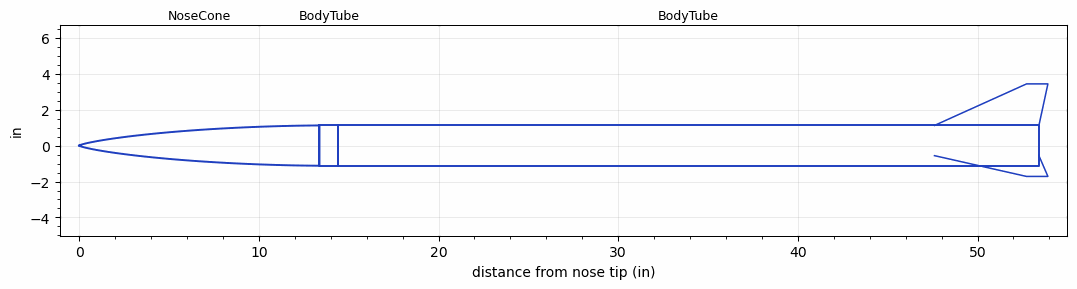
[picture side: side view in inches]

<RASAeroDocument>
 <FileVersion>2</FileVersion>
 <RocketDesign>
  <NoseCone>
   <Length>13.375</Length>
   <Diameter>2.241</Diameter>
   <Shape>LV-Haack</Shape>
   <Location>0</Location>
  </NoseCone>
  <BodyTube>
   <Length>1.0415</Length>
   <Diameter>2.241</Diameter>
   <Location>13.375</Location>
  </BodyTube>
  <BodyTube>
   <Length>39</Length>
   <Diameter>2.241</Diameter>
   <Location>14.4165</Location>
   <Fin>
    <Count>3</Count>
    <Chord>5.813</Chord>
    <Span>2.313</Span>
    <SweepDistance>5.125</SweepDistance>
    <TipChord>1.188</TipChord>
    <Thickness>0.124</Thickness>
    <Location>5.813</Location>
    <AirfoilSection>Hexagonal Blunt Base</AirfoilSection>
    <FX1>0.5</FX1>
   </Fin>
  </BodyTube>
  <Surface>Smooth Paint</Surface>
  <ModifiedBarrowman>True</ModifiedBarrowman>
  <Turbulence>False</Turbulence>
  <UseBooster1>False</UseBooster1>
  <UseBooster2>False</UseBooster2>
 </RocketDesign>
 <LaunchSite>
  <Altitude>1250</Altitude>
  <Pressure>0</Pressure>
  <RodAngle>0</RodAngle>
  <RodLength>6</RodLength>
  <Temperature>90</Temperature>
  <WindSpeed>10</WindSpeed>
 </LaunchSite>
 <Recovery>
  <Altitude1>1000</Altitude1>
  <Altitude2>500</Altitude2>
  <DeviceType1>Parachute</DeviceType1>
  <DeviceType2>Parachute</DeviceType2>
  <Event1>True</Event1>
  <Event2>True</Event2>
  <Size1>6</Size1>
  <Size2>36</Size2>
  <EventType1>Apogee</EventType1>
  <EventType2>Altitude</EventType2>
  <CD1>0.5</CD1>
  <CD2>0.98</CD2>
 </Recovery>
 <SimulationList>
  <Simulation>
   <SustainerEngine>K590  (CTI)</SustainerEngine>
   <SustainerLaunchWt>6.63</SustainerLaunchWt>
   <SustainerCG>32.84</SustainerCG>
   <SustainerIgnitionDelay>0</SustainerIgnitionDelay>
   <Booster1SeparationDelay>0</Booster1SeparationDelay>
   <Booster1IgnitionDelay>0</Booster1IgnitionDelay>
   <IncludeBooster1>False</IncludeBooster1>
   <Booster2Delay>0</Booster2Delay>
   <IncludeBooster2>False</IncludeBooster2>
   <TimetoApogee>32.44056</TimetoApogee>
   <MaxAltitude>24973.27</MaxAltitude>
   <MaxVelocity>2311.566</MaxVelocity>
  </Simulation>
  <Simulation>
   <SustainerEngine>K660  (CTI)</SustainerEngine>
   <SustainerLaunchWt>6.69</SustainerLaunchWt>
   <SustainerCG>31.59</SustainerCG>
   <SustainerIgnitionDelay>0</SustainerIgnitionDelay>
   <Booster1SeparationDelay>0</Booster1SeparationDelay>
   <Booster1IgnitionDelay>0</Booster1IgnitionDelay>
   <IncludeBooster1>False</IncludeBooster1>
   <Booster2Delay>0</Booster2Delay>
   <IncludeBooster2>False</IncludeBooster2>
   <TimetoApogee>32.29059</TimetoApogee>
   <MaxAltitude>24734.03</MaxAltitude>
   <MaxVelocity>2468.057</MaxVelocity>
  </Simulation>
  <Simulation>
   <SustainerEngine>J380SS  (CTI)</SustainerEngine>
   <SustainerLaunchWt>5.23</SustainerLaunchWt>
   <SustainerCG>33.03</SustainerCG>
   <SustainerIgnitionDelay>0</SustainerIgnitionDelay>
   <Booster1SeparationDelay>0</Booster1SeparationDelay>
   <Booster1IgnitionDelay>0</Booster1IgnitionDelay>
   <IncludeBooster1>False</IncludeBooster1>
   <Booster2Delay>0</Booster2Delay>
   <IncludeBooster2>False</IncludeBooster2>
   <TimetoApogee>24.22046</TimetoApogee>
   <MaxAltitude>11923.27</MaxAltitude>
   <MaxVelocity>1436.021</MaxVelocity>
  </Simulation>
  <Simulation>
   <SustainerEngine>K260-CL  (CTI)</SustainerEngine>
   <SustainerLaunchWt>6.88</SustainerLaunchWt>
   <SustainerCG>31.73</SustainerCG>
   <SustainerIgnitionDelay>0</SustainerIgnitionDelay>
   <Booster1SeparationDelay>0</Booster1SeparationDelay>
   <Booster1IgnitionDelay>0</Booster1IgnitionDelay>
   <IncludeBooster1>False</IncludeBooster1>
   <Booster2Delay>0</Booster2Delay>
   <IncludeBooster2>False</IncludeBooster2>
   <TimetoApogee>34.33025</TimetoApogee>
   <MaxAltitude>24319.66</MaxAltitude>
   <MaxVelocity>1773.055</MaxVelocity>
  </Simulation>
  <Simulation>
   <SustainerEngine>K820-BS  (CTI)</SustainerEngine>
   <SustainerLaunchWt>6.56</SustainerLaunchWt>
   <SustainerCG>32.83</SustainerCG>
   <SustainerIgnitionDelay>0</SustainerIgnitionDelay>
   <Booster1SeparationDelay>0</Booster1SeparationDelay>
   <Booster1IgnitionDelay>0</Booster1IgnitionDelay>
   <IncludeBooster1>False</IncludeBooster1>
   <Booster2Delay>0</Booster2Delay>
   <IncludeBooster2>False</IncludeBooster2>
   <TimetoApogee>30.99061</TimetoApogee>
   <MaxAltitude>23556.58</MaxAltitude>
   <MaxVelocity>2620.127</MaxVelocity>
  </Simulation>
  <Simulation>
   <SustainerEngine>L1040LR  (LR)</SustainerEngine>
   <SustainerLaunchWt>8.88</SustainerLaunchWt>
   <SustainerCG>35.15</SustainerCG>
   <SustainerIgnitionDelay>0</SustainerIgnitionDelay>
   <Booster1SeparationDelay>0</Booster1SeparationDelay>
   <Booster1IgnitionDelay>0</Booster1IgnitionDelay>
   <IncludeBooster1>False</IncludeBooster1>
   <Booster2Delay>0</Booster2Delay>
   <IncludeBooster2>False</IncludeBooster2>
   <TimetoApogee>39.21943</TimetoApogee>
   <MaxAltitude>34493.99</MaxAltitude>
   <MaxVelocity>2827.867</MaxVelocity>
  </Simulation>
 </SimulationList>
</RASAeroDocument>
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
